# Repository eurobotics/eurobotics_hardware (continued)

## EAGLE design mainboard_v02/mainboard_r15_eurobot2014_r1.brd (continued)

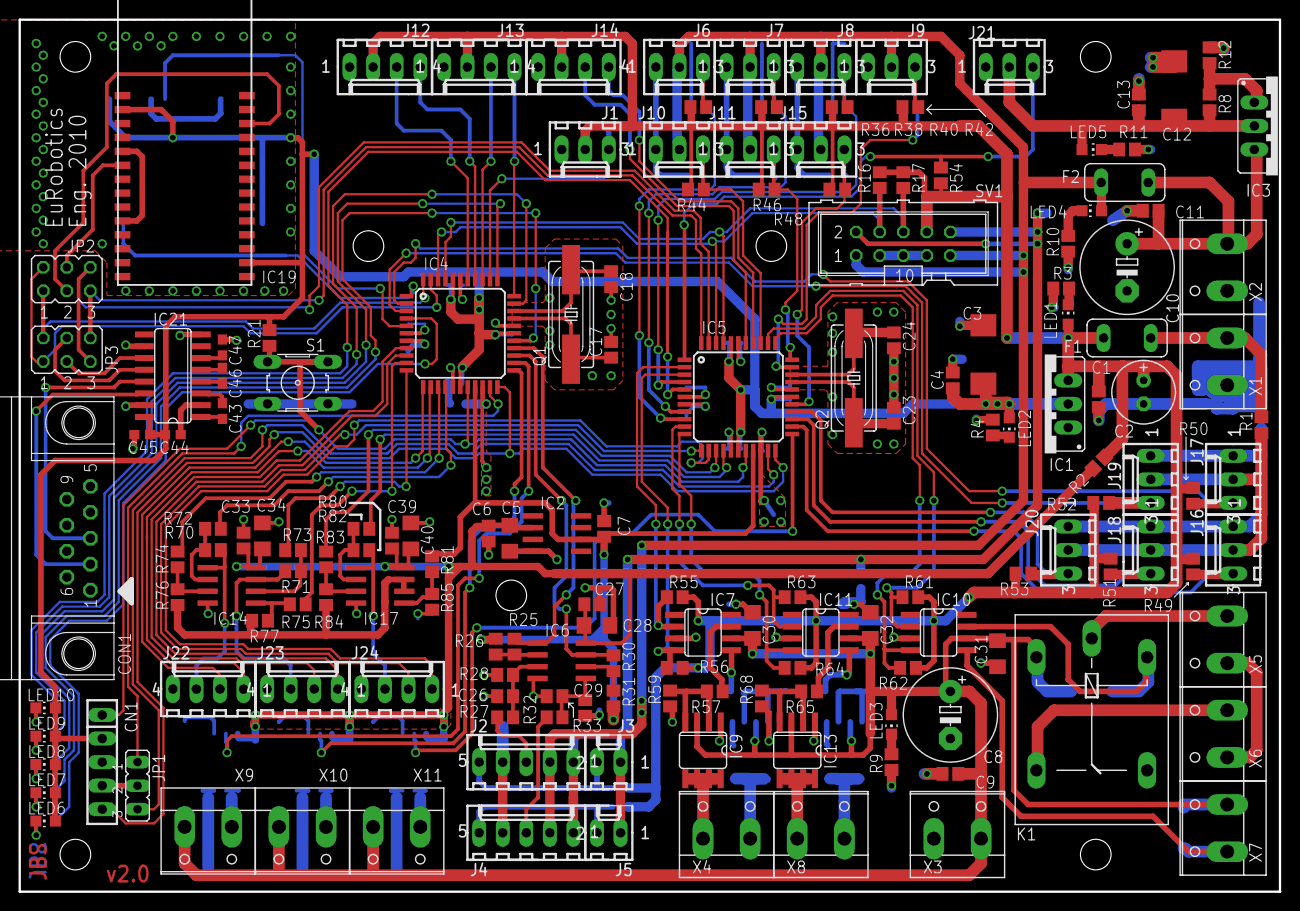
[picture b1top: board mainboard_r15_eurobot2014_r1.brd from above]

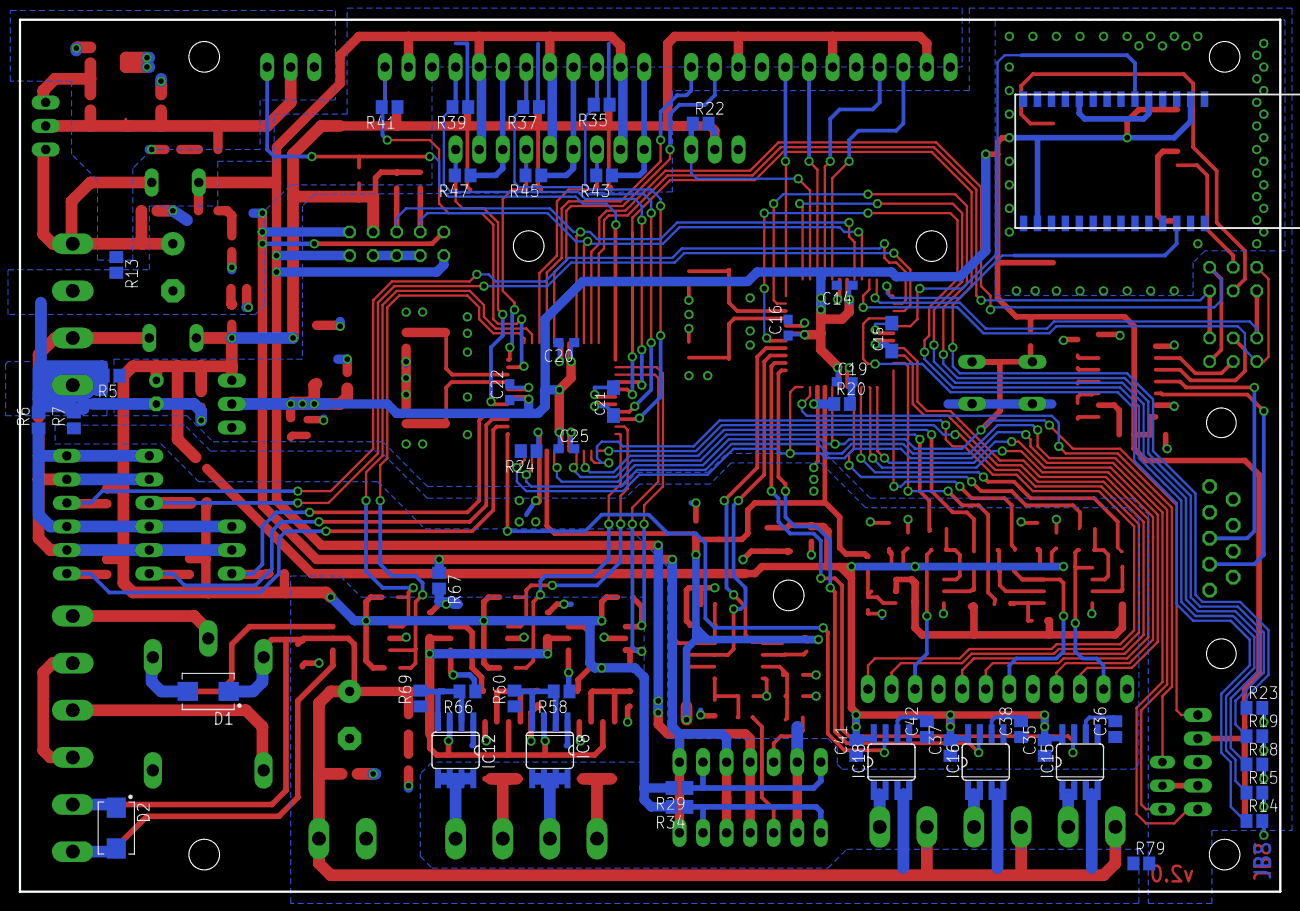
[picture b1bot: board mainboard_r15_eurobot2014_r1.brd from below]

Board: 2 copper layers, 135.9 x 94.0 mm, 211 parts (49 on the bottom side), 150 nets.
